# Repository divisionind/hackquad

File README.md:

# HackQuad
An open-source esp32-based IoT quadcopter intended to be controlled over WiFi (STA or AP) via an xbox controller.

### Why
I made this in 2020, early 2021, because I like building stuff and wanted to test my mechatronics / full-stack product development 
skills. I always planned on open-sourcing it. However, after I got it flying I moved on to other projects and forgot about it.
Today I decided it's about time. I didn't have the heart to clean it up much (kinda nostalgic for me now) so its still 
very much in that dirty development stage. I did organize it for the repo though. I hope this serves as a good reference for anyone
interested in what makes a minimal quadcopter tick -- from the ground up.

### Media

#### [Flight test video](https://www.youtube.com/watch?v=RQggOqLySJw)

### Otherwise unlisted specs
|Part|Description|
|----|-----------|
|Battery|350mAh|
|Motors|8.5x20mm DC|
|Propellers|75mm D (60 works too)|
|USB-C|charging, programming & debugging|
|Frame|PLA+ here, ABS or other gummy polymer|

### Notes

#### The camera
I wired the camera connector up backwards like an idiot, but if you reverse the pin order it should work.

#### Possible improvements
Something to make this project more practical would be dropping the camera, adding a better imu w/ magnetometer, a several watt
RGB led, larger battery, maybe GPS, etc... and using the mesh networking capability of the espressif chips to make a very 
cheap drone light show platform. I say maybe GPS because dead-reckoning imu data combined w/ rssi info in a massive cluster might be
enough to get stable quad-to-quad relative positional information (saving on cost of the individual unit).

#### Improvements for this implementation
- neutral boyancy
- better IMU w/ magnometer
- proper multi-position IMU calibration routine to correct for axes skew
- linear acceleration control layer
- better battery capacity estimation

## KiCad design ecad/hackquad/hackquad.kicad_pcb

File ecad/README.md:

# hackquad_hardware
The PCB revision says MK4, but I was being very liberal w/ what constitutes a version back then. This
was my 2nd ever PCB while learning electronics design, and I'd do a lot different today.

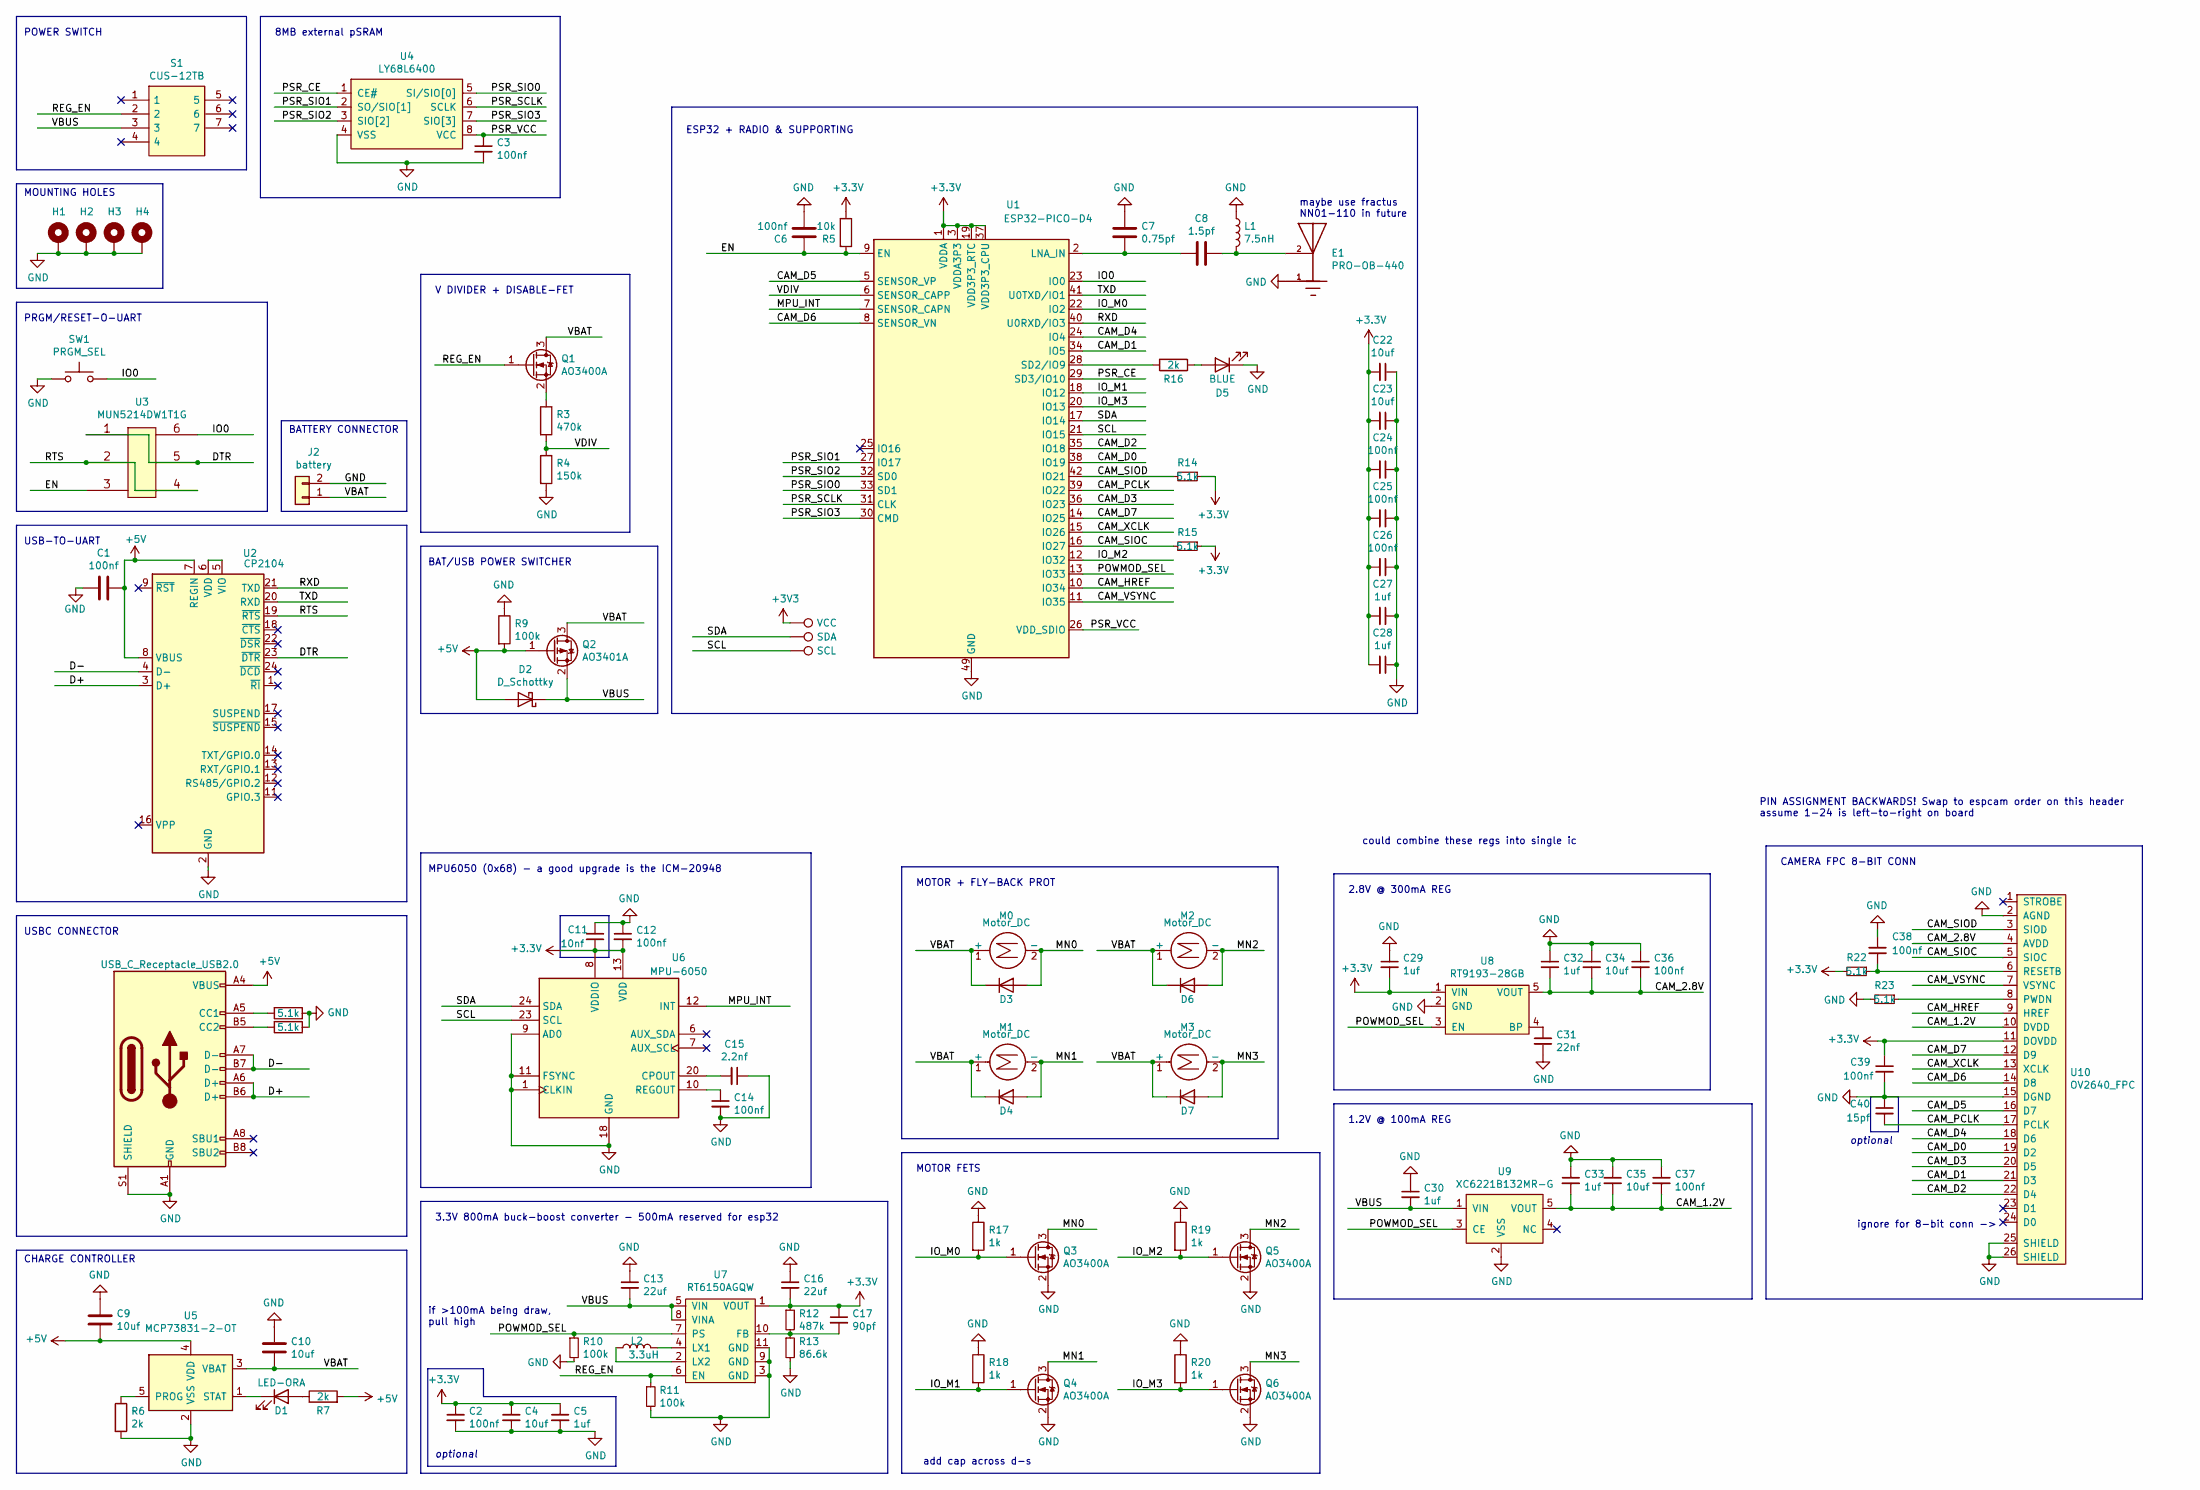
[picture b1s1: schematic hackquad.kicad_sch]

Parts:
C1, C2, C3, C6, C24, C25, C26, C36, C37, C38, C39: 100nf; C_0402_1005Metric
C4, C9, C10, C22, C23, C34, C35: 10uf; C_0402_1005Metric
C5, C27, C28, C29, C30, C32, C33: 1uf; C_0402_1005Metric
C7: 0.75pf; C_0402_1005Metric
C8: 1.5pf; C_0402_1005Metric
C11: 10nf; C_0402_1005Metric; LCSC C60133
C12, C14: 100nf; C_0402_1005Metric; LCSC C60474
C13, C16: 22uf; C_1206_3216Metric; LCSC C386064
C15: 2.2nf; C_0402_1005Metric; LCSC C513667
C17: 90pf; C_0402_1005Metric
C31: 22nf; C_0402_1005Metric
C40: 15pf; C_0402_1005Metric
D1: LED-ORA; LED_0603_1608Metric; LCSC C2286
D2: D_Schottky; D_SOD-123; LCSC` C8598
D3, D4, D6, D7: D; D_SOD-123F; LCSC C64898
D5: BLUE; LED_0603_1608Metric; LCSC C72041
E1: PRO-OB-440; ANT_PRO-OB-440; PARTREV 3.2
H1, H2, H3, H4: MountingHole_Pad; MountingHole_2.2mm_M2_Pad_Via
J1: USB_C_Receptacle_USB2.0; USB_C_Receptacle_HRO_TYPE-C-31-M-12; LCSC C165948
J2: battery; battery_pads
L1: 7.5nH; L_0402_1005Metric; LCSC C341696
L2: 3.3uH; L_4x4x3mm; LCSC C36409/C340390
M0, M1, M2, M3: Motor_DC; PinHeader_1x02_P2.54mm_Vertical
Q1, Q3, Q4, Q5, Q6: AO3400A; SOT-23
Q2: AO3401A; SOT-23; LCSC C347476
R1, R2, R14, R15, R22, R23: 5.1k; R_0402_1005Metric
R3: 470k; R_0402_1005Metric; LCSC C25790
R4: 150k; R_0402_1005Metric; LCSC C25755
R5: 10k; R_0402_1005Metric
R6, R7, R16: 2k; R_0402_1005Metric
R9, R10, R11: 100k; R_0402_1005Metric
R12: 487k; R_0402_1005Metric
R13: 86.6k; R_0402_1005Metric
R17, R18, R19, R20: 1k; R_0402_1005Metric
S1: CUS-12TB; CUS-12B; Manufacturer_Part_Number CUS-12TB
SW1: PRGM_SEL; pushbutton_TS-1185EC-C-D-B; LCSC C318893
TP1: VCC; TestPoint_Pad_D1.0mm
TP3: SDA; TestPoint_Pad_D1.0mm
TP4: SCL; TestPoint_Pad_D1.0mm
U1: ESP32-PICO-D4; QFN-48-1EP_7x7mm_P0.5mm_EP5.3x5.3mm
U2: CP2104; QFN-24-1EP_4x4mm_P0.5mm_EP2.6x2.6mm
U3: MUN5214DW1T1G; SOT-363_SC-70-6; LCSC C94403
U4: LY68L6400; SOP-8_3.9x4.9mm_P1.27mm; LCSC C261881
U5: MCP73831-2-OT; SOT-23-5; LCSC C424093
U6: MPU-6050; InvenSense_QFN-24_4x4mm_P0.5mm
U7: RT6150AGQW; WDFN-10L_3x3
U8: RT9193-28GB; SOT-23-5; LCSC C56731
U9: XC6221B132MR-G; SOT-23-5; LCSC C16613
U10: OV2640_FPC; FPC_24_AFC01-S24FCC-00; LCSC C262276

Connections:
+3V3: C2.1, C4.1, C5.1, C11.2, C12.2, C16.2, C17.1, C22.2, C23.2, C24.2, C25.2, C26.2, C27.2, C28.2, C29.2, C39.1, R5.2, R12.1, R14.1, R15.1, R22.2, TP1.1, U1.1 (VDDA), U1.3 (VDDA3P3), U1.4 (VDDA3P3), U1.19 (VDD3P3_RTC), U1.37 (VDD3P3_CPU), U1.43 (VDDA), U1.46 (VDDA), U6.8 (VDDIO), U6.13 (VDD), U7.1 (VOUT), U8.1 (VIN), U10.11 (DOVDD)
+5V: C1.1, C9.2, D2.2 (A), J1.A4 (VBUS), J1.A9 (VBUS), J1.B4 (VBUS), J1.B9 (VBUS), Q2.1 (G), R7.2, R9.2, U2.7 (REGIN), U2.8 (VBUS), U5.4 (VDD)
/CAM_1.2V: C33.2, C35.2, C37.2, U9.5 (VOUT), U10.10 (DVDD)
/CAM_2.8V: C32.2, C34.2, C36.2, U8.5 (VOUT), U10.4 (AVDD)
/CAM_D0: U1.38 (IO19), U10.19 (D2)
/CAM_D1: U1.34 (IO5), U10.21 (D3)
/CAM_D2: U1.35 (IO18), U10.22 (D4)
/CAM_D3: U1.36 (IO23), U10.20 (D5)
/CAM_D4: U1.24 (IO4), U10.18 (D6)
/CAM_D5: U1.5 (SENSOR_VP), U10.16 (D7)
/CAM_D6: U1.8 (SENSOR_VN), U10.14 (D8)
/CAM_D7: U1.14 (IO25), U10.12 (D9)
/CAM_HREF: U1.10 (IO34), U10.9 (HREF)
/CAM_PCLK: C40.2, U1.39 (IO22), U10.17 (PCLK)
/CAM_SIOC: R15.2, U1.16 (IO27), U10.5 (SIOC)
/CAM_SIOD: R14.2, U1.42 (IO21), U10.3 (SIOD)
/CAM_VSYNC: U1.11 (IO35), U10.7 (VSYNC)
/CAM_XCLK: U1.15 (IO26), U10.13 (XCLK)
/D+: J1.A6 (D+), J1.B6 (D+), U2.3 (D+)
/D-: J1.A7 (D-), J1.B7 (D-), U2.4 (D-)
/DTR: U2.23 (~DTR), U3.1, U3.5
/EN: C6.1, R5.1, U1.9 (EN), U3.3
/IO0: SW1.2, U1.23 (IO0), U3.6
/IO_M0: Q3.1 (G), R17.2, U1.22 (IO2)
/IO_M1: Q4.1 (G), R18.2, U1.18 (IO12)
/IO_M2: Q5.1 (G), R19.2, U1.12 (IO32)
/IO_M3: Q6.1 (G), R20.2, U1.20 (IO13)
/MN0: D3.2 (A), M0.2 (-), Q3.3 (D)
/MN1: D4.2 (A), M1.2 (-), Q4.3 (D)
/MN2: D6.2 (A), M2.2 (-), Q5.3 (D)
/MN3: D7.2 (A), M3.2 (-), Q6.3 (D)
/MPU_INT: U1.7 (SENSOR_CAPN), U6.12 (INT)
/POWMOD_SEL: R10.1, U1.13 (IO33), U7.7 (PS), U8.3 (EN), U9.3 (CE)
/PSR_CE: U1.29 (SD3/IO10), U4.1 (CE#)
/PSR_SCLK: U1.31 (CLK), U4.6 (SCLK)
/PSR_SIO0: U1.33 (SD1), U4.5 (SI/SIO[0])
/PSR_SIO1: U1.27 (IO17), U4.2 (SO/SIO[1])
/PSR_SIO2: U1.32 (SD0), U4.3 (SIO[2])
/PSR_SIO3: U1.30 (CMD), U4.7 (SIO[3])
/PSR_VCC: C3.1, U1.26 (VDD_SDIO), U4.8 (VCC)
/REG_EN: Q1.1 (G), R11.1, S1.2, U7.6 (EN)
/RTS: U2.19 (~RTS), U3.2, U3.4
/RXD: U1.40 (U0RXD/IO3), U2.21 (TXD)
/SCL: TP4.1, U1.21 (IO15), U6.23 (SCL)
/SDA: TP3.1, U1.17 (IO14), U6.24 (SDA)
/TXD: U1.41 (U0TXD/IO1), U2.20 (RXD)
/VBAT: C10.2, D3.1 (K), D4.1 (K), D6.1 (K), D7.1 (K), J2.1, M0.1 (+), M1.1 (+), M2.1 (+), M3.1 (+), Q1.3 (D), Q2.3 (D), U5.3 (VBAT)
/VBUS: C13.2, C30.2, D2.1 (K), Q2.2 (S), S1.3, U7.5 (VIN), U7.8 (VINA), U9.1 (VIN)
/VDIV: R3.2, R4.1, U1.6 (SENSOR_CAPP)
GND: C1.2, C2.2, C3.2, C4.2, C5.2, C6.2, C7.1, C9.1, C10.1, C11.1, C12.1, C13.1, C14.2, C15.1, C16.1, C22.1, C23.1, C24.1, C25.1, C26.1, C27.1, C28.1, C29.1, C30.1, C31.2, C32.1, C33.1, C34.1, C35.1, C36.1, C37.1, C38.1, C39.2, C40.1, D5.1 (K), E1.1, H1.1, H2.1, H3.1, H4.1, J1.A1 (GND), J1.A12 (GND), J1.B1 (GND), J1.B12 (GND), J1.S1 (SHIELD), J2.2, L1.1, Q3.2 (S), Q4.2 (S), Q5.2 (S), Q6.2 (S), R1.1, R2.1, R4.2, R6.2, R9.1, R10.2, R11.2, R13.2, R17.1, R18.1, R19.1, R20.1, R23.2, SW1.1, U1.49 (GND), U2.2 (GND), U2.25 (GND), U4.4 (VSS), U5.2 (VSS), U6.1 (CLKIN), U6.9 (AD0), U6.11 (FSYNC), U6.18 (GND), U7.3 (GND), U7.9 (GND), U7.11 (GND), U8.2 (GND), U9.2 (VSS), U10.2 (AGND), U10.15 (DGND), U10.25 (SHIELD), U10.26 (SHIELD)
unnamed: C7.2, C8.2, U1.2 (LNA_IN)
unnamed: C8.1, E1.2, L1.2
unnamed: C14.1, U6.10 (REGOUT)
unnamed: C15.2, U6.20 (CPOUT)
unnamed: C17.2, R12.2, R13.1, U7.10 (FB)
unnamed: C31.1, U8.4 (BP)
unnamed: C38.2, R22.1, U10.6 (RESETB)
unnamed: D1.1 (K), U5.1 (STAT)
unnamed: D1.2 (A), R7.1
unnamed: D5.2 (A), R16.1
unnamed: J1.A5 (CC1), R1.2
unnamed: J1.B5 (CC2), R2.2
unnamed: L2.1, U7.2 (LX2)
unnamed: L2.2, U7.4 (LX1)
unnamed: Q1.2 (S), R3.1
unnamed: R6.1, U5.5 (PROG)
unnamed: R16.2, U1.28 (SD2/IO9)
unnamed: R23.1, U10.8 (PWDN)
unnamed: U2.5 (VIO), U2.6 (VDD)

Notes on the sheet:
MPU6050 (0x68) - a good upgrade is the ICM-20948
CHARGE CONTROLLER
POWER SWITCH
1.2V @ 100mA REG
MOTOR FETS
MOUNTING HOLES
V DIVIDER + DISABLE-FET
MOTOR + FLY-BACK PROT
3.3V 800mA buck-boost converter - 500mA reserved for esp32
optional
if >100mA being draw, pull high
2.8V @ 300mA REG
add cap across d-s
USB-TO-UART
USBC CONNECTOR
8MB external pSRAM
PRGM/RESET-O-UART
PIN ASSIGNMENT BACKWARDS! Swap to espcam order on this header assume 1-24 is left-to-right on board
BATTERY CONNECTOR
BAT/USB POWER SWITCHER
CAMERA FPC 8-BIT CONN
maybe use fractus NN01-110 in future
ignore for 8-bit conn ->
could combine these regs into single ic
ESP32 + RADIO & SUPPORTING

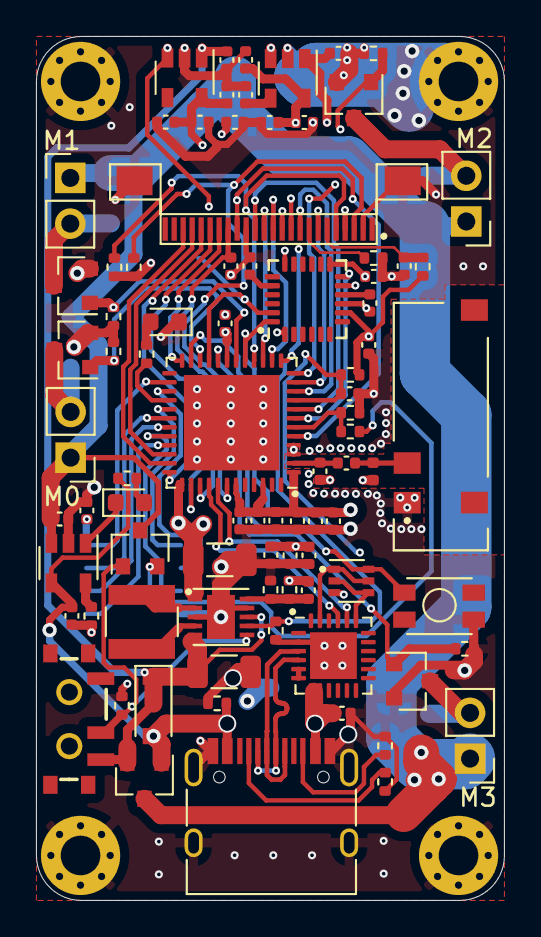
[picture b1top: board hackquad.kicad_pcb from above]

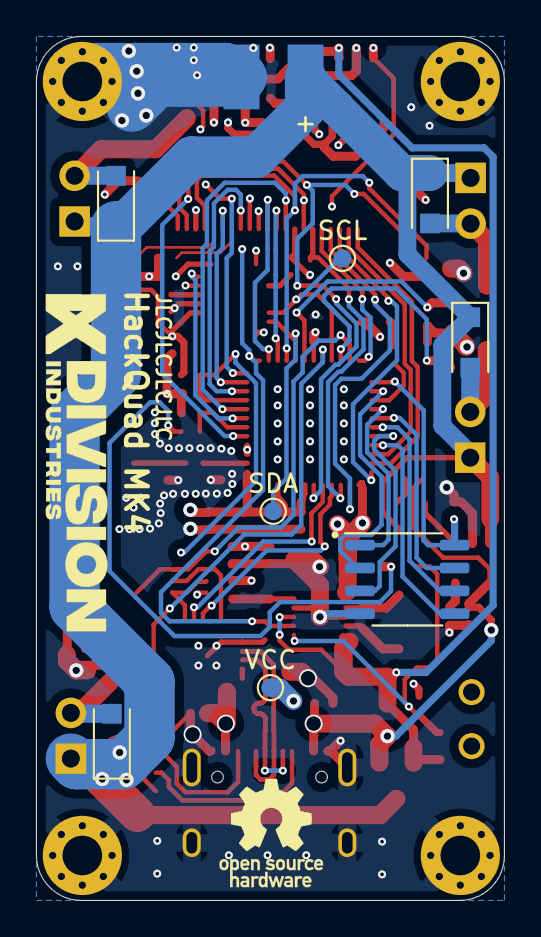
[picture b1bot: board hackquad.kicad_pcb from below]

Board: 4 copper layers, 26.0 x 48.0 mm, 98 parts (9 on the bottom side), 69 nets.

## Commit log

2022-12-03 initial release
